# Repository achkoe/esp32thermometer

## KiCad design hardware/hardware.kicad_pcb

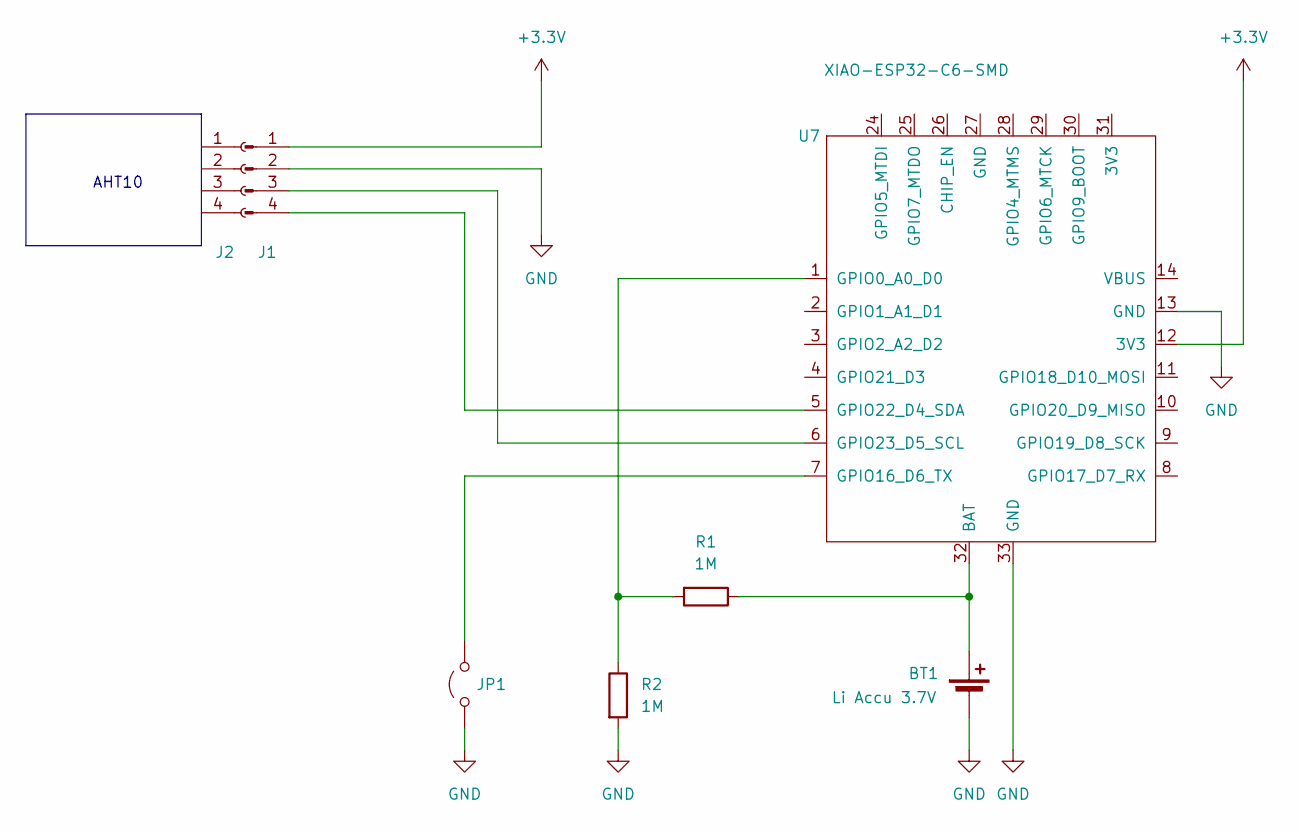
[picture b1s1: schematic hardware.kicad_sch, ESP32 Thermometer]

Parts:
BT1: Li Accu 3.7V; BatteryHolder_Eagle_12BH611-GR
J1: Conn_01x04_Pin; PinSocket_1x04_P2.54mm_Horizontal
J2: Conn_01x04_Socket; PinSocket_1x04_P2.54mm_Horizontal
JP1: Jumper_2_Open; Jumper_Harwin_S1621_P10.9mm
R1, R2: 1M; R_Axial_DIN0411_L9.9mm_D3.6mm_P20.32mm_Horizontal
U7: XIAO-ESP32-C6-SMD

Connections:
+3.3V: J1.1, U7.12 (3V3)
GND: BT1.2 (-), J1.2, JP1.1 (A), R2.2, U7.13 (GND), U7.33 (GND)
unnamed: BT1.1 (+), R1.1, U7.32 (BAT)
unnamed: J1.3, U7.6 (GPIO23_D5_SCL)
unnamed: J1.4, U7.5 (GPIO22_D4_SDA)
unnamed: JP1.2 (B), U7.7 (GPIO16_D6_TX)
unnamed: R1.2, R2.1, U7.1 (GPIO0_A0_D0)

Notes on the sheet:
AHT10

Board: 2 copper layers, 27 parts (0 on the bottom side), 7 nets, no tracks yet.

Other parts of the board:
U1: XIAO-SAMD21-SMD
U2: XIAO-RP2040-SMD
U3: XIAO-nRF52840-SMD
U4: XIAO-SAMD21-DIP
U5: XIAO-RP2040-DIP
U6: XIAO-nRF52840-DIP
U8: XIAO-ESP32-C3-SMD
U9: XIAO-ESP32-S3-SMD
U10: XIAO-ESP32-C6-DIP
U11: XIAO-ESP32-S3-DIP
U12: XIAO-ESP32-C3-DIP
U13: XIAO-RP2350-SMD
U14: XIAO-R4-SMD
U16: XIAO-RP2350-DIP
U17: XIAO-R4-DIP
U18: XIAO-ESP32-C5-SMD
U19: XIAO-ESP32-S3-Plus-SMD
U20: XIAO-MG24-SMD
U21: XIAO-nRF54l15-SMD
U22: XIAO-nRF52840-Plus-SMD
